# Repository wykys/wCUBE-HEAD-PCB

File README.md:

# wCUBE-HEAD-PCB
PCB for the head of my 3D printer.

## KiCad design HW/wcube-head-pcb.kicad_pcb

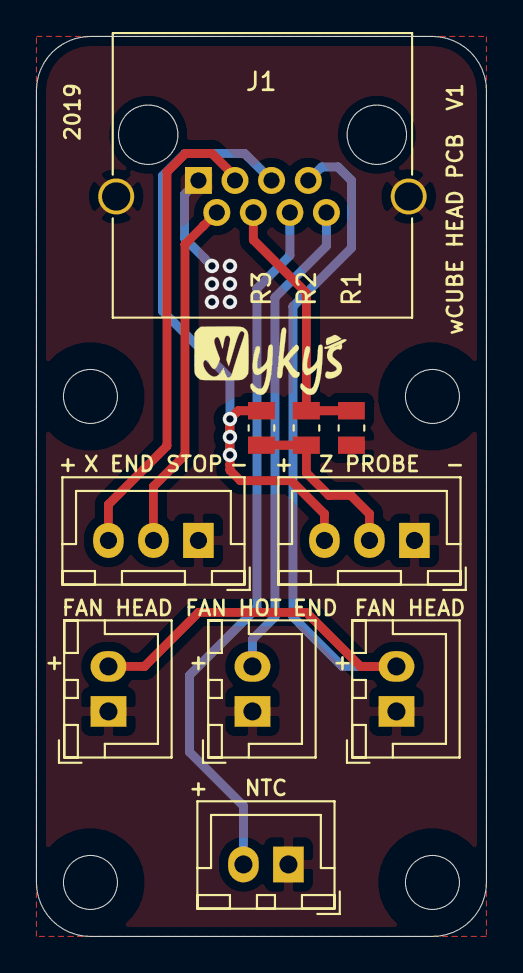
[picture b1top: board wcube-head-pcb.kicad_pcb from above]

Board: 2 copper layers, 25.0 x 50.0 mm, 15 parts (0 on the bottom side), 9 nets.

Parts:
GR1: Wykys; wykys_small_skill
H1, H2, H3, H4: M3; Bolt_M3
J1: RJ45; RJ45_TE_1-406541-1
J2: NTC; JST_XH_B02B-XH-A_1x02_P2.50mm_Vertical
J3: X END STOP; JST_XH_B03B-XH-A_1x03_P2.50mm_Vertical
J4: FAN HOT END; JST_XH_B02B-XH-A_1x02_P2.50mm_Vertical
J5: FAN HEAD A; JST_XH_B02B-XH-A_1x02_P2.50mm_Vertical
J6: FAN HEAD B; JST_XH_B02B-XH-A_1x02_P2.50mm_Vertical
J7: PROBE; JST_XH_B03B-XH-A_1x03_P2.50mm_Vertical
R1: 100k; R_0805_2012Metric
R2: 150k; R_0805_2012Metric
R3: 10k; R_0805_2012Metric

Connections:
+5V: J1.3, J3.3
+12V: J1.5, J7.3, R3.2
/FAN-HEAD: J1.7, J5.2, J6.2
/FAN-HOT-END: J1.8, J4.2
/NTC: J1.6, J2.2
/PROBE: J1.4, R1.2, R2.2
/X-END-STOP: J1.2, J3.2
GND: J1.1, J1.9, J2.1, J3.1, J4.1, J5.1, J6.1, J7.1, R1.1
unnamed: J7.2, R2.1, R3.1

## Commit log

2019-02-12 Added KiCAD project
2019-02-12 Added GERBER files
2019-02-12 Added PDF schematic
